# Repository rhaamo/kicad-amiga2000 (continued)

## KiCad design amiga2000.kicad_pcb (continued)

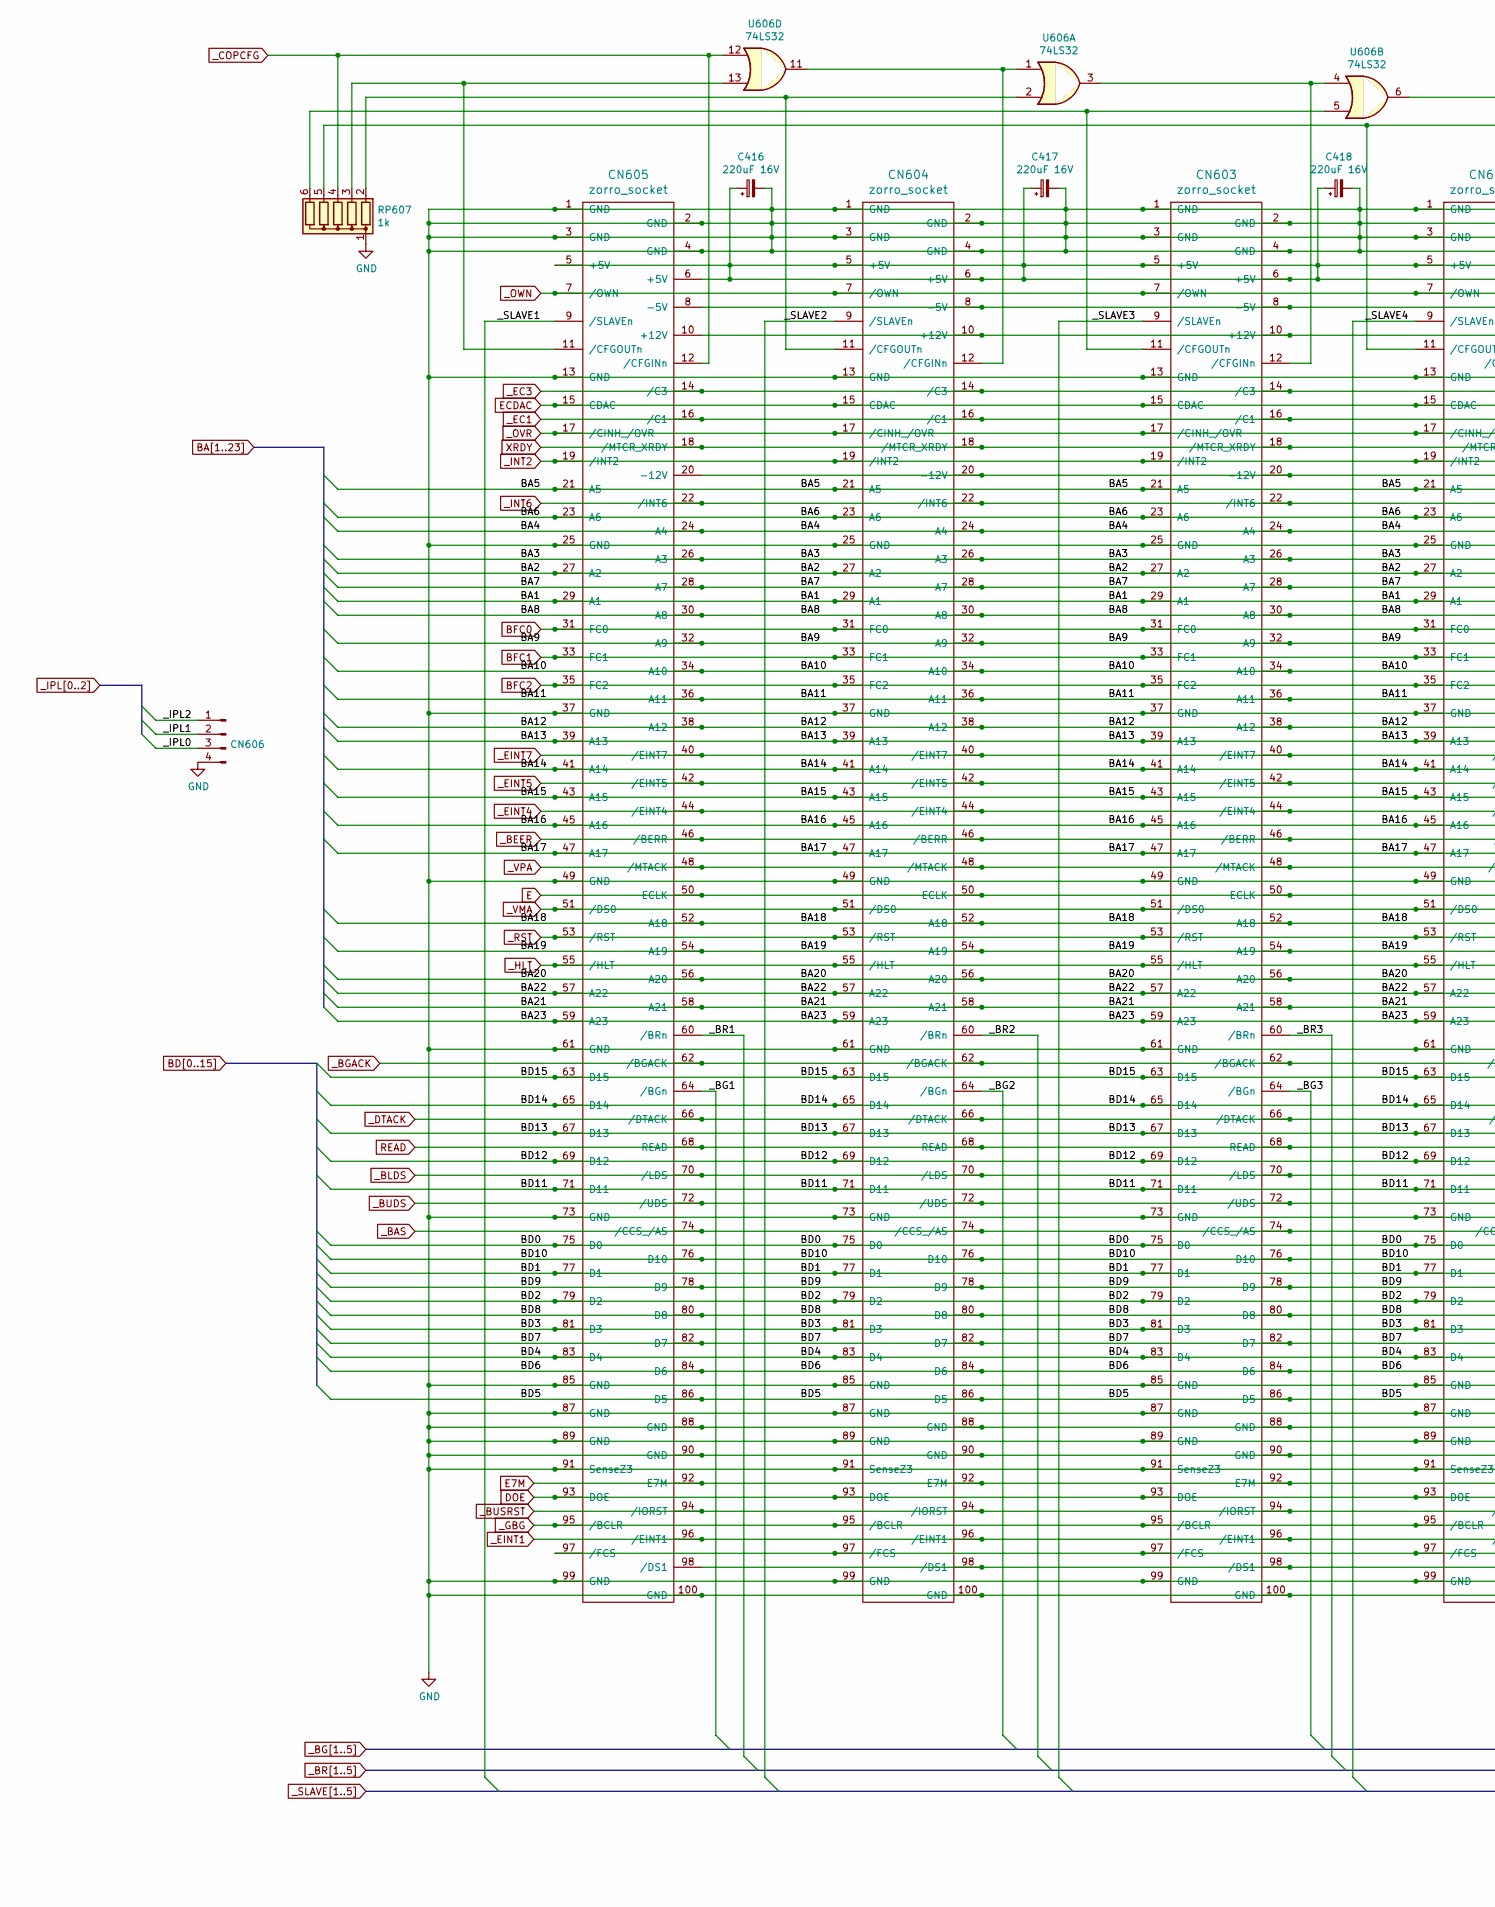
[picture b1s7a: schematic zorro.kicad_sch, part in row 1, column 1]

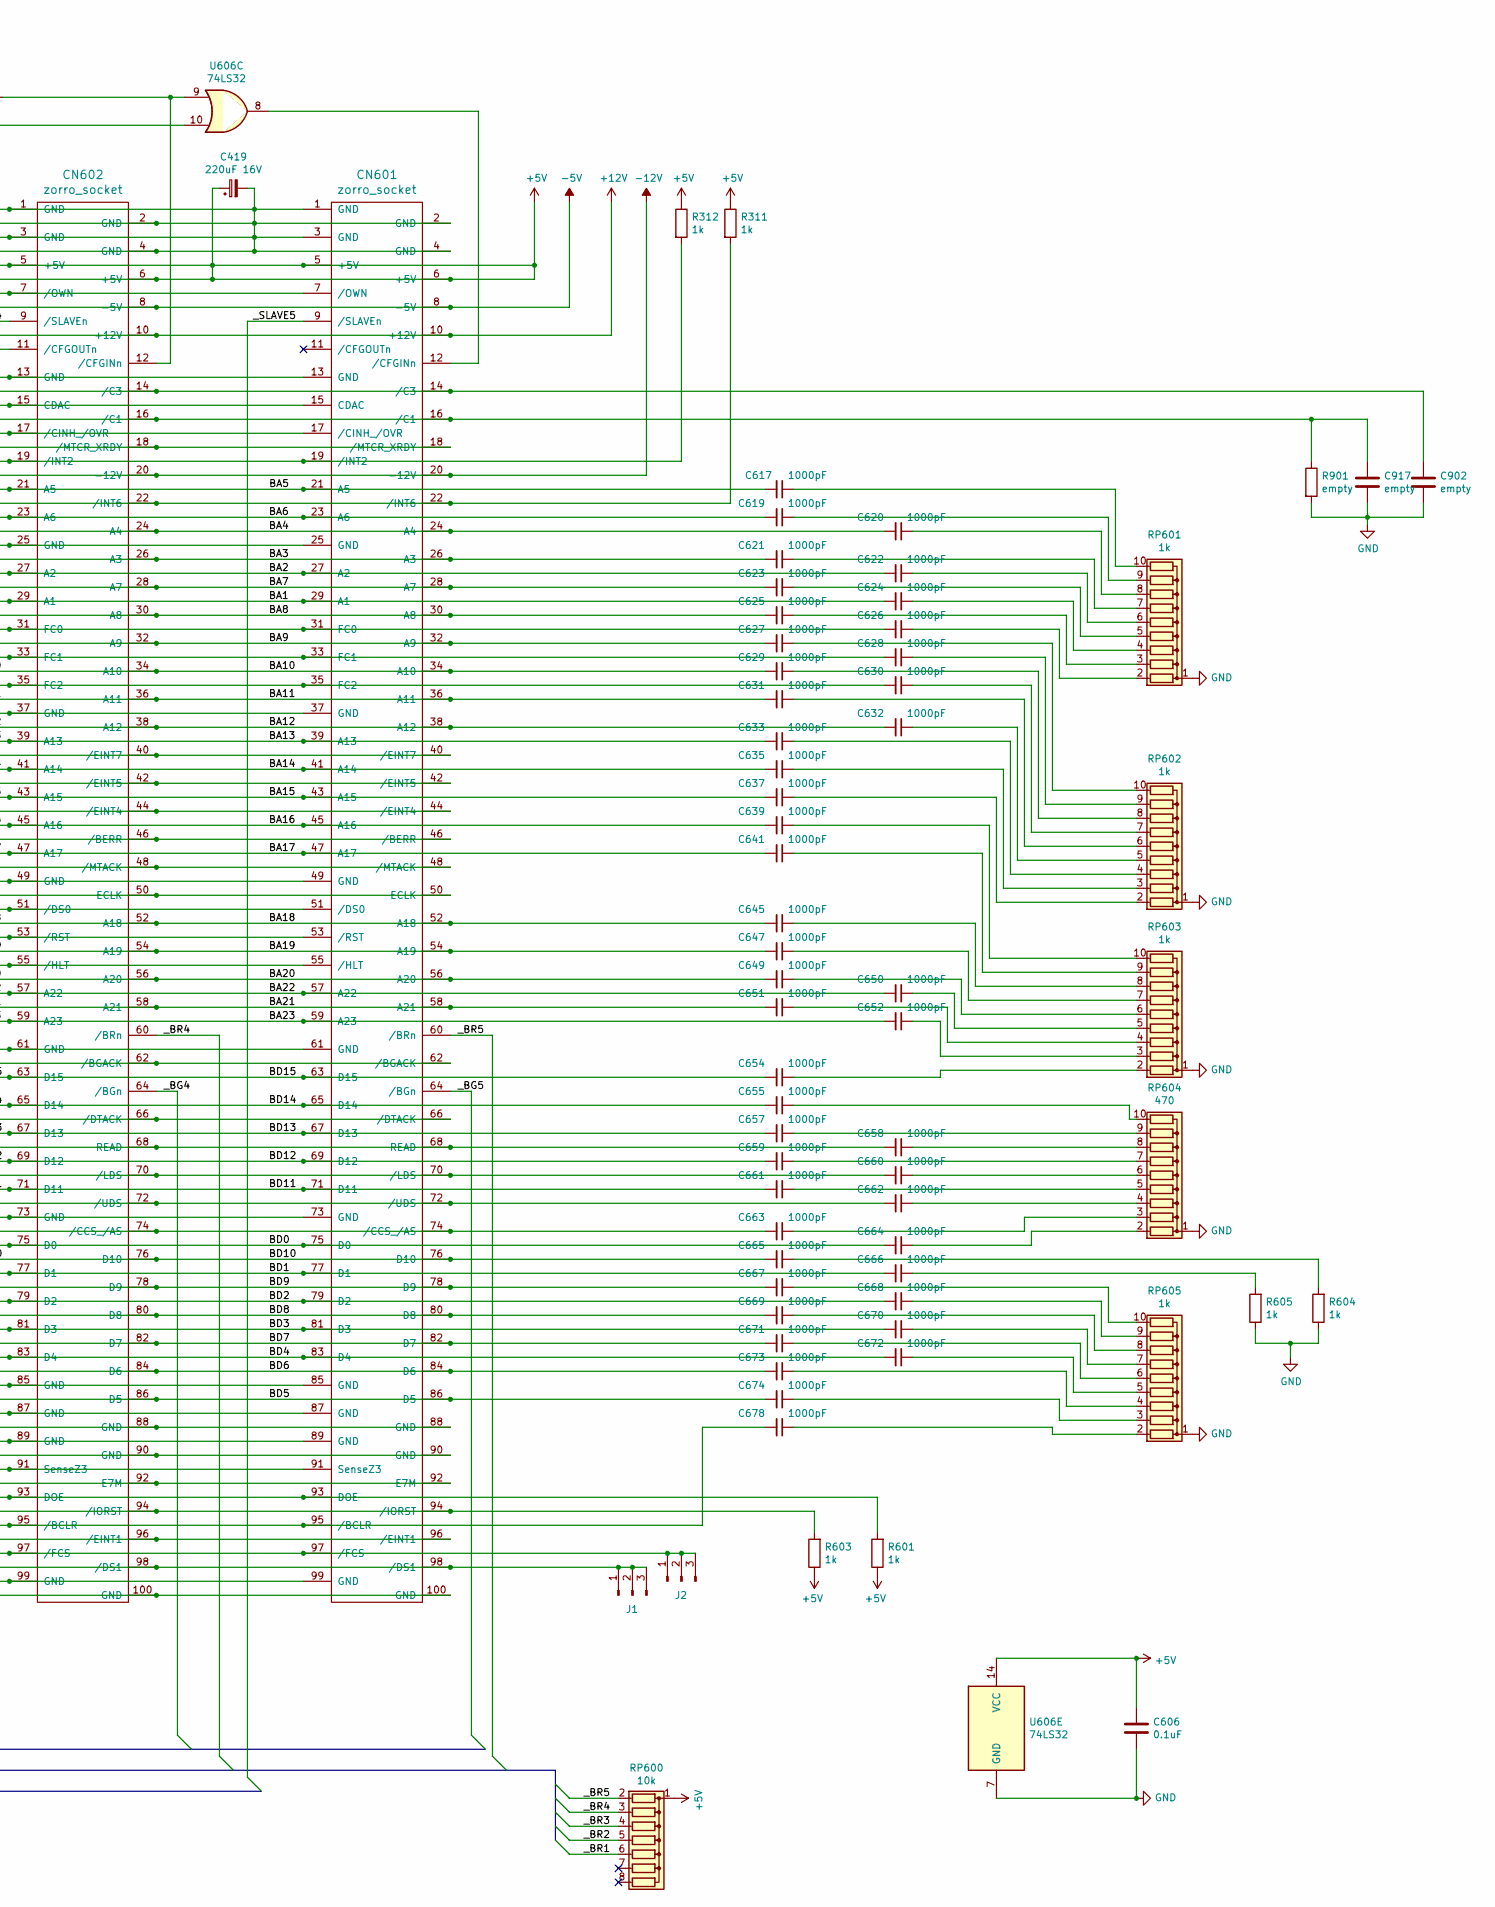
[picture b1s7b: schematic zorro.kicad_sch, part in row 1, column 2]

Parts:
C416, C417, C418, C419: 220uF 16V; C_Axial_L19.0mm_D8.0mm_P25.00mm_Horizontal
C606: 0.1uF; C_Rect_L11.5mm_W2.6mm_P10.00mm_MKT
C617, C619, C620, C621, C622, C623, C624, C625, C626, C627, C628, C629, C630, C631, C632, C633, C635, C637, C639, C641, C645, C647, C649, C650, C651, C652, C654, C655, C657, C658, C659, C660, C661, C662, C663, C664, C665, C666, C667, C668, C669, C670, C671, C672, C673, C674, C678: 1000pF; C_Rect_L11.5mm_W2.0mm_P10.00mm_MKT
C902, C917: empty; C_Rect_L11.5mm_W2.0mm_P10.00mm_MKT
CN601, CN602, CN603, CN604, CN605: zorro_socket; Zorro
CN606: Conn_01x04_Male; PinHeader_1x04_P2.54mm_Vertical
J1, J2: Conn_01x03_Male; PinHeader_1x03_P2.54mm_Vertical
R311, R312, R601, R603, R604, R605: 1k; R_Axial_DIN0207_L6.3mm_D2.5mm_P10.16mm_Horizontal
R901: empty; R_Axial_DIN0207_L6.3mm_D2.5mm_P10.16mm_Horizontal
RP600: 10k; R_Array_SIP8
RP601, RP602, RP603, RP605: 1k; R_Array_SIP10
RP604: 470; R_Array_SIP10
RP607: 1k; R_Array_SIP6
U606: 74LS32; DIP-14_W7.62mm_Socket

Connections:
+12V: CN601.10 (+12V), CN602.10 (+12V), CN603.10 (+12V), CN604.10 (+12V), CN605.10 (+12V); also elsewhere on the board
-5V: CN601.8 (-5V), CN602.8 (-5V), CN603.8 (-5V), CN604.8 (-5V), CN605.8 (-5V); also elsewhere on the board
-12V: CN601.20 (-12V), CN602.20 (-12V), CN603.20 (-12V), CN604.20 (-12V), CN605.20 (-12V); also elsewhere on the board
BA1: C624.2, CN601.29 (A1), CN602.29 (A1), CN603.29 (A1), CN604.29 (A1), CN605.29 (A1); also elsewhere on the board
BA2: C622.2, CN601.27 (A2), CN602.27 (A2), CN603.27 (A2), CN604.27 (A2), CN605.27 (A2); also elsewhere on the board
BA3: C621.2, CN601.26 (A3), CN602.26 (A3), CN603.26 (A3), CN604.26 (A3), CN605.26 (A3); also elsewhere on the board
BA4: C620.2, CN601.24 (A4), CN602.24 (A4), CN603.24 (A4), CN604.24 (A4), CN605.24 (A4); also elsewhere on the board
BA5: C617.2, CN601.21 (A5), CN602.21 (A5), CN603.21 (A5), CN604.21 (A5), CN605.21 (A5); also elsewhere on the board
BA6: C619.2, CN601.23 (A6), CN602.23 (A6), CN603.23 (A6), CN604.23 (A6), CN605.23 (A6); also elsewhere on the board
BA7: C623.2, CN601.28 (A7), CN602.28 (A7), CN603.28 (A7), CN604.28 (A7), CN605.28 (A7); also elsewhere on the board
BA8: C625.2, CN601.30 (A8), CN602.30 (A8), CN603.30 (A8), CN604.30 (A8), CN605.30 (A8); also elsewhere on the board
BA9: C627.2, CN601.32 (A9), CN602.32 (A9), CN603.32 (A9), CN604.32 (A9), CN605.32 (A9); also elsewhere on the board
BA10: C629.2, CN601.34 (A10), CN602.34 (A10), CN603.34 (A10), CN604.34 (A10), CN605.34 (A10); also elsewhere on the board
BA11: C631.2, CN601.36 (A11), CN602.36 (A11), CN603.36 (A11), CN604.36 (A11), CN605.36 (A11); also elsewhere on the board
BA12: C632.2, CN601.38 (A12), CN602.38 (A12), CN603.38 (A12), CN604.38 (A12), CN605.38 (A12); also elsewhere on the board
BA13: C633.2, CN601.39 (A13), CN602.39 (A13), CN603.39 (A13), CN604.39 (A13), CN605.39 (A13); also elsewhere on the board
BA14: C635.2, CN601.41 (A14), CN602.41 (A14), CN603.41 (A14), CN604.41 (A14), CN605.41 (A14); also elsewhere on the board
BA15: C637.2, CN601.43 (A15), CN602.43 (A15), CN603.43 (A15), CN604.43 (A15), CN605.43 (A15); also elsewhere on the board
BA16: C639.2, CN601.45 (A16), CN602.45 (A16), CN603.45 (A16), CN604.45 (A16), CN605.45 (A16); also elsewhere on the board
BA17: C641.2, CN601.47 (A17), CN602.47 (A17), CN603.47 (A17), CN604.47 (A17), CN605.47 (A17); also elsewhere on the board
BA18: C645.2, CN601.52 (A18), CN602.52 (A18), CN603.52 (A18), CN604.52 (A18), CN605.52 (A18); also elsewhere on the board
BA19: C647.2, CN601.54 (A19), CN602.54 (A19), CN603.54 (A19), CN604.54 (A19), CN605.54 (A19); also elsewhere on the board
BA20: C649.2, CN601.56 (A20), CN602.56 (A20), CN603.56 (A20), CN604.56 (A20), CN605.56 (A20); also elsewhere on the board
BA21: C651.2, CN601.58 (A21), CN602.58 (A21), CN603.58 (A21), CN604.58 (A21), CN605.58 (A21); also elsewhere on the board
BA22: C650.2, CN601.57 (A22), CN602.57 (A22), CN603.57 (A22), CN604.57 (A22), CN605.57 (A22); also elsewhere on the board
BA23: C652.2, CN601.59 (A23), CN602.59 (A23), CN603.59 (A23), CN604.59 (A23), CN605.59 (A23); also elsewhere on the board
BD0: C664.2, CN601.75 (D0), CN602.75 (D0), CN603.75 (D0), CN604.75 (D0), CN605.75 (D0); also elsewhere on the board
BD1: C666.2, CN601.77 (D1), CN602.77 (D1), CN603.77 (D1), CN604.77 (D1), CN605.77 (D1); also elsewhere on the board
BD2: C668.2, CN601.79 (D2), CN602.79 (D2), CN603.79 (D2), CN604.79 (D2), CN605.79 (D2); also elsewhere on the board
BD3: C670.2, CN601.81 (D3), CN602.81 (D3), CN603.81 (D3), CN604.81 (D3), CN605.81 (D3); also elsewhere on the board
BD4: C672.2, CN601.83 (D4), CN602.83 (D4), CN603.83 (D4), CN604.83 (D4), CN605.83 (D4); also elsewhere on the board
BD5: C674.2, CN601.86 (D5), CN602.86 (D5), CN603.86 (D5), CN604.86 (D5), CN605.86 (D5); also elsewhere on the board
BD6: C673.2, CN601.84 (D6), CN602.84 (D6), CN603.84 (D6), CN604.84 (D6), CN605.84 (D6); also elsewhere on the board
BD7: C671.2, CN601.82 (D7), CN602.82 (D7), CN603.82 (D7), CN604.82 (D7), CN605.82 (D7); also elsewhere on the board
BD8: C669.2, CN601.80 (D8), CN602.80 (D8), CN603.80 (D8), CN604.80 (D8), CN605.80 (D8); also elsewhere on the board
BD9: C667.2, CN601.78 (D9), CN602.78 (D9), CN603.78 (D9), CN604.78 (D9), CN605.78 (D9); also elsewhere on the board
BD10: C665.2, CN601.76 (D10), CN602.76 (D10), CN603.76 (D10), CN604.76 (D10), CN605.76 (D10); also elsewhere on the board
BD11: C661.2, CN601.71 (D11), CN602.71 (D11), CN603.71 (D11), CN604.71 (D11), CN605.71 (D11); also elsewhere on the board
BD12: C659.2, CN601.69 (D12), CN602.69 (D12), CN603.69 (D12), CN604.69 (D12), CN605.69 (D12); also elsewhere on the board
BD13: C657.2, CN601.67 (D13), CN602.67 (D13), CN603.67 (D13), CN604.67 (D13), CN605.67 (D13); also elsewhere on the board
BD14: C655.2, CN601.65 (D14), CN602.65 (D14), CN603.65 (D14), CN604.65 (D14), CN605.65 (D14); also elsewhere on the board
BD15: C654.2, CN601.63 (D15), CN602.63 (D15), CN603.63 (D15), CN604.63 (D15), CN605.63 (D15); also elsewhere on the board
BFC0: C626.2, CN601.31 (FC0), CN602.31 (FC0), CN603.31 (FC0), CN604.31 (FC0), CN605.31 (FC0); also elsewhere on the board
BFC1: C628.2, CN601.33 (FC1), CN602.33 (FC1), CN603.33 (FC1), CN604.33 (FC1), CN605.33 (FC1); also elsewhere on the board
BFC2: C630.2, CN601.35 (FC2), CN602.35 (FC2), CN603.35 (FC2), CN604.35 (FC2), CN605.35 (FC2); also elsewhere on the board
DOE: CN601.93 (DOE), CN602.93 (DOE), CN603.93 (DOE), CN604.93 (DOE), CN605.93 (DOE), R601.2; also elsewhere on the board
E: CN601.50 (ECLK), CN602.50 (ECLK), CN603.50 (ECLK), CN604.50 (ECLK), CN605.50 (ECLK); also elsewhere on the board
E7M: CN601.92 (E7M), CN602.92 (E7M), CN603.92 (E7M), CN604.92 (E7M), CN605.92 (E7M); also elsewhere on the board
ECDAC: CN601.15 (CDAC), CN602.15 (CDAC), CN603.15 (CDAC), CN604.15 (CDAC), CN605.15 (CDAC); also elsewhere on the board
GND: C416.2, C417.2, C418.2, C419.2, C606.2, C902.2, C917.2, CN601.1 (GND), CN601.2 (GND), CN601.3 (GND), CN601.4 (GND), CN601.13 (GND), CN601.25 (GND), CN601.37 (GND), CN601.49 (GND), CN601.61 (GND), CN601.73 (GND), CN601.85 (GND), CN601.87 (GND), CN601.88 (GND), CN601.89 (GND), CN601.90 (GND), CN601.91 (SenseZ3), CN601.99 (GND), CN601.100 (GND), CN602.1 (GND), CN602.2 (GND), CN602.3 (GND), CN602.4 (GND), CN602.13 (GND), CN602.25 (GND), CN602.37 (GND), CN602.49 (GND), CN602.61 (GND), CN602.73 (GND), CN602.85 (GND), CN602.87 (GND), CN602.88 (GND), CN602.89 (GND), CN602.90 (GND), CN602.91 (SenseZ3), CN602.99 (GND), CN602.100 (GND), CN603.1 (GND), CN603.2 (GND), CN603.3 (GND), CN603.4 (GND), CN603.13 (GND), CN603.25 (GND), CN603.37 (GND), CN603.49 (GND), CN603.61 (GND), CN603.73 (GND), CN603.85 (GND), CN603.87 (GND), CN603.88 (GND), CN603.89 (GND), CN603.90 (GND), CN603.91 (SenseZ3), CN603.99 (GND), CN603.100 (GND), CN604.1 (GND), CN604.2 (GND), CN604.3 (GND), CN604.4 (GND), CN604.13 (GND), CN604.25 (GND), CN604.37 (GND), CN604.49 (GND), CN604.61 (GND), CN604.73 (GND), CN604.85 (GND), CN604.87 (GND), CN604.88 (GND), CN604.89 (GND), CN604.90 (GND), CN604.91 (SenseZ3), CN604.99 (GND), CN604.100 (GND), CN605.1 (GND), CN605.2 (GND), CN605.3 (GND), CN605.4 (GND), CN605.13 (GND), CN605.25 (GND), CN605.37 (GND), CN605.49 (GND), CN605.61 (GND), CN605.73 (GND), CN605.85 (GND), CN605.87 (GND), CN605.88 (GND), CN605.89 (GND), CN605.90 (GND), CN605.91 (SenseZ3), CN605.99 (GND), CN605.100 (GND), CN606.4, R604.1, R605.1, R901.2, RP601.1 (common), RP602.1 (common), RP603.1 (common), RP604.1 (common), RP605.1 (common), RP607.1 (common), U606.7 (GND); also elsewhere on the board
unnamed: C617.1, RP601.10 (R9)
unnamed: C619.1, RP601.9 (R8)
unnamed: C620.1, RP601.8 (R7)
unnamed: C621.1, RP601.7 (R6)
unnamed: C622.1, RP601.6 (R5)
unnamed: C623.1, RP601.5 (R4)
unnamed: C624.1, RP601.4 (R3)
unnamed: C625.1, RP601.3 (R2)
unnamed: C626.1, RP601.2 (R1)
unnamed: C627.1, RP602.10 (R9)
unnamed: C628.1, RP602.9 (R8)
unnamed: C629.1, RP602.8 (R7)
unnamed: C630.1, RP602.7 (R6)
unnamed: C631.1, RP602.6 (R5)
unnamed: C632.1, RP602.5 (R4)
unnamed: C633.1, RP602.4 (R3)
unnamed: C635.1, RP602.3 (R2)
unnamed: C637.1, RP602.2 (R1)
unnamed: C639.1, RP603.10 (R9)
unnamed: C641.1, RP603.9 (R8)
unnamed: C645.1, RP603.8 (R7)
unnamed: C647.1, RP603.7 (R6)
unnamed: C649.1, RP603.6 (R5)
unnamed: C650.1, RP603.5 (R4)
unnamed: C651.1, RP603.4 (R3)
unnamed: C652.1, RP603.3 (R2)
unnamed: C654.1, RP603.2 (R1)
unnamed: C655.1, RP604.10 (R9)
unnamed: C657.1, RP604.9 (R8)
unnamed: C658.1, RP604.8 (R7)
unnamed: C659.1, RP604.7 (R6)
unnamed: C660.1, RP604.6 (R5)
unnamed: C661.1, RP604.5 (R4)
unnamed: C662.1, RP604.4 (R3)
unnamed: C663.1, RP604.3 (R2)
unnamed: C664.1, RP604.2 (R1)
unnamed: C665.1, R604.2
unnamed: C666.1, R605.2
unnamed: C667.1, RP605.10 (R9)
unnamed: C668.1, RP605.9 (R8)
unnamed: C669.1, RP605.8 (R7)
unnamed: C670.1, RP605.7 (R6)
unnamed: C671.1, RP605.6 (R5)
unnamed: C672.1, RP605.5 (R4)
unnamed: C673.1, RP605.4 (R3)
unnamed: C674.1, RP605.3 (R2)
unnamed: C678.1, RP605.2 (R1)
unnamed: CN601.12 (/CFGINn), U606.8
unnamed: CN601.97 (/FCS), CN602.97 (/FCS), CN603.97 (/FCS), CN604.97 (/FCS), CN605.97 (/FCS), J2.1, J2.2, J2.3
unnamed: CN601.98 (/DS1), CN602.98 (/DS1), CN603.98 (/DS1), CN604.98 (/DS1), CN605.98 (/DS1), J1.1, J1.2, J1.3
unnamed: CN602.11 (/CFGOUTn), RP607.5 (R4), U606.10
unnamed: CN602.12 (/CFGINn), U606.6, U606.9
unnamed: CN603.11 (/CFGOUTn), RP607.6 (R5), U606.5
unnamed: CN603.12 (/CFGINn), U606.3, U606.4
unnamed: CN604.11 (/CFGOUTn), RP607.2 (R1), U606.2
unnamed: CN604.12 (/CFGINn), U606.1, U606.11
unnamed: CN605.11 (/CFGOUTn), RP607.3 (R2), U606.13
READ: C658.2, CN601.68 (READ), CN602.68 (READ), CN603.68 (READ), CN604.68 (READ), CN605.68 (READ); also elsewhere on the board
XRDY: CN601.18 (/MTCR_XRDY), CN602.18 (/MTCR_XRDY), CN603.18 (/MTCR_XRDY), CN604.18 (/MTCR_XRDY), CN605.18 (/MTCR_XRDY); also elsewhere on the board
_BAS: C663.2, CN601.74 (/CCS_/AS), CN602.74 (/CCS_/AS), CN603.74 (/CCS_/AS), CN604.74 (/CCS_/AS), CN605.74 (/CCS_/AS); also elsewhere on the board
_BEER: CN601.46 (/BERR), CN602.46 (/BERR), CN603.46 (/BERR), CN604.46 (/BERR), CN605.46 (/BERR); also elsewhere on the board
_BG1: CN605.64 (/BGn); also elsewhere on the board
_BG2: CN604.64 (/BGn); also elsewhere on the board
_BG3: CN603.64 (/BGn); also elsewhere on the board
_BG4: CN602.64 (/BGn); also elsewhere on the board
_BG5: CN601.64 (/BGn); also elsewhere on the board
_BGACK: CN601.62 (/BGACK), CN602.62 (/BGACK), CN603.62 (/BGACK), CN604.62 (/BGACK), CN605.62 (/BGACK); also elsewhere on the board
_BLDS: C660.2, CN601.70 (/LDS), CN602.70 (/LDS), CN603.70 (/LDS), CN604.70 (/LDS), CN605.70 (/LDS); also elsewhere on the board
_BR1: CN605.60 (/BRn), RP600.6 (R5); also elsewhere on the board
_BR2: CN604.60 (/BRn), RP600.5 (R4); also elsewhere on the board
_BR3: CN603.60 (/BRn), RP600.4 (R3); also elsewhere on the board
_BR4: CN602.60 (/BRn), RP600.3 (R2); also elsewhere on the board
_BR5: CN601.60 (/BRn), RP600.2 (R1); also elsewhere on the board
_BUDS: C662.2, CN601.72 (/UDS), CN602.72 (/UDS), CN603.72 (/UDS), CN604.72 (/UDS), CN605.72 (/UDS); also elsewhere on the board
_BUSRST: CN601.94 (/IORST), CN602.94 (/IORST), CN603.94 (/IORST), CN604.94 (/IORST), CN605.94 (/IORST), R603.2; also elsewhere on the board
_COPCFG: CN605.12 (/CFGINn), RP607.4 (R3), U606.12; also elsewhere on the board
_DTACK: CN601.66 (/DTACK), CN602.66 (/DTACK), CN603.66 (/DTACK), CN604.66 (/DTACK), CN605.66 (/DTACK); also elsewhere on the board
_EC1: C917.1, CN601.16 (/C1), CN602.16 (/C1), CN603.16 (/C1), CN604.16 (/C1), CN605.16 (/C1), R901.1; also elsewhere on the board
_EC3: C902.1, CN601.14 (/C3), CN602.14 (/C3), CN603.14 (/C3), CN604.14 (/C3), CN605.14 (/C3); also elsewhere on the board
_EINT1: CN601.96 (/EINT1), CN602.96 (/EINT1), CN603.96 (/EINT1), CN604.96 (/EINT1), CN605.96 (/EINT1); also elsewhere on the board
_EINT4: CN601.44 (/EINT4), CN602.44 (/EINT4), CN603.44 (/EINT4), CN604.44 (/EINT4), CN605.44 (/EINT4); also elsewhere on the board
_EINT5: CN601.42 (/EINT5), CN602.42 (/EINT5), CN603.42 (/EINT5), CN604.42 (/EINT5), CN605.42 (/EINT5); also elsewhere on the board
_EINT7: CN601.40 (/EINT7), CN602.40 (/EINT7), CN603.40 (/EINT7), CN604.40 (/EINT7), CN605.40 (/EINT7); also elsewhere on the board
_GBG: C678.2, CN601.95 (/BCLR), CN602.95 (/BCLR), CN603.95 (/BCLR), CN604.95 (/BCLR), CN605.95 (/BCLR); also elsewhere on the board
_HLT: CN601.55 (/HLT), CN602.55 (/HLT), CN603.55 (/HLT), CN604.55 (/HLT), CN605.55 (/HLT); also elsewhere on the board
_INT2: CN601.19 (/INT2), CN602.19 (/INT2), CN603.19 (/INT2), CN604.19 (/INT2), CN605.19 (/INT2), R312.2; also elsewhere on the board
_INT6: CN601.22 (/INT6), CN602.22 (/INT6), CN603.22 (/INT6), CN604.22 (/INT6), CN605.22 (/INT6), R311.2; also elsewhere on the board
_IPL0: CN606.3; also elsewhere on the board
_IPL1: CN606.2; also elsewhere on the board
_IPL2: CN606.1; also elsewhere on the board
_OVR: CN601.17 (/CINH_/OVR), CN602.17 (/CINH_/OVR), CN603.17 (/CINH_/OVR), CN604.17 (/CINH_/OVR), CN605.17 (/CINH_/OVR); also elsewhere on the board
_OWN: CN601.7 (/OWN), CN602.7 (/OWN), CN603.7 (/OWN), CN604.7 (/OWN), CN605.7 (/OWN); also elsewhere on the board
_RST: CN601.53 (/RST), CN602.53 (/RST), CN603.53 (/RST), CN604.53 (/RST), CN605.53 (/RST); also elsewhere on the board
_SLAVE1: CN605.9 (/SLAVEn); also elsewhere on the board
_SLAVE2: CN604.9 (/SLAVEn); also elsewhere on the board
_SLAVE3: CN603.9 (/SLAVEn); also elsewhere on the board
_SLAVE4: CN602.9 (/SLAVEn); also elsewhere on the board
_SLAVE5: CN601.9 (/SLAVEn); also elsewhere on the board
_VMA: CN601.51 (/DS0), CN602.51 (/DS0), CN603.51 (/DS0), CN604.51 (/DS0), CN605.51 (/DS0); also elsewhere on the board
_VPA: CN601.48 (/MTACK), CN602.48 (/MTACK), CN603.48 (/MTACK), CN604.48 (/MTACK), CN605.48 (/MTACK); also elsewhere on the board
